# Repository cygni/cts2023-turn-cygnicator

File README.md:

# Introduction

Hello and welcome to the CTS 2023 embedded trail. In this trail you will be introduced to basic real-time system concepts and how to utilize them in FreeRTOS, a real-time system core for embedded devices. With these concepts, you will finalize a mini version of a car's telltale: brake, hazard and turn indicators will all be implemented using light and sound that can be controlled from a circuit board.

- [Introduction](#introduction)
  - [Raspberry Pi Pico](#raspberry-pi-pico)
  - [The Circuit Board (PCB)](#the-circuit-board-pcb)
    - [GPIO configuration table](#gpio-configuration-table)
  - [Workshop goals](#workshop-goals)
- [Workshop preparation](#workshop-preparation)
- [Workshop](#workshop)
  - [Preparation](#preparation)
  - [Prepare the development environment](#prepare-the-development-environment)
  - [How to build an image](#how-to-build-an-image)
  - [How to flash an image to Pico](#how-to-flash-an-image-to-pico)
    - [Step 1: Enter programming mode](#step-1-enter-programming-mode)
    - [Step 2: Flash image](#step-2-flash-image)
      - [Flashing using picotool](#flashing-using-picotool)
      - [Flashing by moving UF2 to mass-storage device](#flashing-by-moving-uf2-to-mass-storage-device)
- [Workshop starts here](#workshop-starts-here)
  - [Pico SDK API - Interrupt Handling](#pico-sdk-api---interrupt-handling)
    - [Cygnicator API](#cygnicator-api)
    - [FreeRTOS Task API](#freertos-task-api)
      - [xTaskCreate()](#xtaskcreate)
      - [vTaskStartScheduler()](#vtaskstartscheduler)
      - [vTaskDelay()](#vtaskdelay)
  - [Interrupt Handling](#interrupt-handling)
  - [Step 1: Handle button commands](#step-1-handle-button-commands)
    - [Task scheduling](#task-scheduling)
  - [Step 2: TURN LEFT and TURN RIGHT](#step-2-turn-left-and-turn-right)
    - [Syncing tasks](#syncing-tasks)
  - [Step 3: Hazzard](#step-3-hazzard)
  - [Step 4: Buzzer (TICK/TOCK sound)](#step-4-buzzer-ticktock-sound)
  - [Step 5: Periodicity](#step-5-periodicity)
    - [Handle shared resources](#handle-shared-resources)
  - [Step 6: Break button](#step-6-break-button)
  - [Step 7: One Task that controlls each LED row](#step-7-one-task-that-controlls-each-led-row)

## Raspberry Pi Pico

To realize the project, we will use a Raspberry Pi Pico. The Pico is based on the RP2040 microcontroller, which has a dual-core Arm Cortex-M0 CPU at 133Mhz (though clocked at 125Mhz by default). It has 264kB RAM and 2MB flash memory. The rest of the specifications can be read [here](https://www.raspberrypi.com/documentation/microcontrollers/rp2040.html). Pico has a logic voltage of 3.3V, which means that a GPIO pin that is high will have a voltage of 3.3V.

The board has 28 GPIO pins. GPIO pins are software-controlled connectors that can be used as input or output. Some pins can be used either as GPIO or for other functions such as I2C or PWM to configure it.

NOTE: When we refer to GPIO pins, we mean what is written in the green boxes in the reference image of the Picon, which corresponds to another physical pin (the gray boxes).

Some interesting pins:

- VBUS is connected directly to the micro-USB port and measures 5V when you have a USB adapter connected.
- VSYS is connected to VBUS via a diode. It is possible to drive the Pico directly by soldering a 1.8V to 5.5V voltage source to VSYS if you don't like USB. A Switching Mode Power Supply then converts the input voltage to 3.3V which powers the Pico.
- The 3V3_EN(able) pin can connect to ground to turn off the voltage converter, and then the Pico stops.
- The 3V3 pin is connected to the 3.3V operating voltage and can be used to drive components, the datasheet recommends not to draw more than 300mA.
The RUN pin can be used to restart the Pico, if connected to ground.

Others are described in the data sheet if you are interested.

The PICO has a BOOTSEL button. If you hold it down when you start the Pico, it is put into programmer mode, and appears as a portable USB disk.

## The Circuit Board (PCB)

On the circuit board, you can find a Raspberry Pi Pico that is routed in the PCB to be able to read input from 4 buttons and control 16 orange LEDs & 1 buzzer. Input/output is handled in the GPIO configuration that is *purposely* abstracted from the participants of this trail.

There is also a fifth button closest to the Pico board. This button ties RUN pin to ground when pressed which restarts the Pico.

### GPIO configuration table

Skip this section if you are not interested in which GPIO is connected to what.

| GPIO | GPIO CONFIG | HW desc |
| ---- |---- |------- |
| 2    | OUT | LED_FL0 |
| 3    | OUT | LED_FL1 |
| 4    | OUT | LED_FL2 |
| 5    | OUT | LED_FL3 |
| 6    | OUT | LED_FR0 |
| 7    | OUT | LED_FR1 |
| 8    | OUT | LED_FR2 |
| 9    | OUT | LED_FR3 |
| 10   | OUT | LED_RL0 |
| 11   | OUT | LED_RL1 |
| 12   | OUT | LED_RL2 |
| 13   | OUT | LED_RL3 |
| 19   | OUT | LED_RR0 |
| 18   | OUT | LED_RR1 |
| 17   | OUT | LED_RR2 |
| 16   | OUT | LED_RR3 |
| 14   | IN / PULL-UP | L_INDCR_BTN |
| 15   | IN / PULL-UP| L_INDCR_BTN |
| 20   | IN / PULL-UP| BRAKE_BTN |
| 21   | IN / PULL-UP| HAZARD_BTN |
| 22   | OUT / PWM | BUZZER |

Raspberry Pi Pico is not driving all LEDs directly, instead a MOSFET transistor is used for each LED to drive each individual LED using the +5V from the USB bus. This setup makes it possible for the 3.3V GPIO to control an LED with +5V forward voltage.

Simplification of the parameters:
- R_LED regulates the current that drives the LED i.e. the brightness
- R_PULLDOWN makes sure that the gate is closed by default. It "pulls" down the gate voltage to ground.
- R_GATE regulates the speed at which the MOSFET gate opens. (Other parameters affect this as well e.g. input impedance, internal GPIO resistors etc.)

## Workshop goals

| Button | Action | Expected outcome |
| ------ | ------ | --------- |
| Turn left | On press | Front left & rear left headlights toggles at a fixed interval. Buzzer plays a tick sound for each flash. |
| Turn right | On press | Front right & rear right headlights toggles at a fixed interval. Buzzer plays a tick sound for each flash. |
| Hazard | On press | All headlights headlights toggles at a fixed interval. Buzzer plays a tick sound for each flash. |
| Brake | On hold | All headlights are on. |

By fixed interval in the table above we mean it should be toggled at 1Hz. For the turn indicator, this would be according to the time diagram below. Note that we don't include tock sound. Cooler car brands do this. We don't know why:

Here is a gif of how the results will look like:
!!!TODO ADD A GIF WITH REFERENCE SOLUTION!!!

In a normal car, when the hazard is on and the brake is issued, the hazard continues after the brake has been released. In this workshop we do not require this behavior instead it's up to the designer how to handle this. You will see in the time diagrams later in the workshop that we suggest that you need to reissue the hazard after braking. The same goes for turn indicator.

# Workshop preparation

Prepare the workshop

## Preparation

This section is where you prepare and set up your development environment.
At the end of this section, you should be able to know where to add changes, and how to build and flash. To test the circuit board, we have provided a blinky code example that is going to be flashed onto the board.

Important folders and files:
```bash
# Your workspace, feel free to add more workspaces if needed.
firmware/turn-cygnicator

# ..we suggest you work in the same workspace throughout the workshop
# since every step builds on the previous one.

# Main entrypoint to your solution
firmware/turn-cygnicator/main.c

# Binary image that will be flashed onto the Raspberry Pi Pico
firmware/turn-cygnicator/turn-cygnicator.uf2

# Cygni turnindicator (Cygnicator) APIs
firmware/inc

# FreeRTOS kernel, you shouldn't need to touch this
firmware/lib/FreeRTOS-Kernel

# FreeRTOS configuration file for this project, you shouldn't need to touch this
firmware/inc/FreeRTOSConfig.h

```

## Prepare the development environment

In other words, build the docker image (`firmware/docker/Dockerfile`) that contains the FreeRTOS kernel, pico SDK, picotool and other tools/libraries that are needed.

Run this command in the root folder of this repository:
`docker build --build-arg UID="$(id -u)" -t rpisdk:latest docker/` or run
`build_docker.sh`

It takes a couple of minutes to download all dependencies, this command should only be run once.

## How to build an image

```bash
cd firmware

./build.sh

# Expected output
=== Output Files ===
./firmware/build/turn-cygnicator/turn-cygnicator.uf2
./firmware/build/blinky-demo/blinky-demo.uf2
```

## How to flash an image to Pico

### Step 1: Enter programming mode

Before flashing the image, the Pico needs to enter its programming mode.
This is done by holding the BOOTSEL button (1/RED) and pressing the RESET button (2/BLUE) once while the BOOTSEL button is still held down.

Now the Pico should have entered programming mode, it should appear to your host computer as a mass-storage device, like a USB memory stick. If it doesn't, you need to redo step 1.

### Step 2: Flash image

There are two alternatives to flash in this guide.

Either use:
- **picotool** provided in the docker image 
- **move UF2 image manually** to the mass-storage device.

#### Flashing using picotool

For convenience, we have included a flash script that shortens the command that is needed to flash.
Flash blinky sample code to verify that communication towards Pico works:
```bash
cd firmware

./flash.sh blinky-demo/blinky-demo.uf2
```

The expected results should look like this:

..by default this command flashes `turn-cygnicator` workspace, which is where your implementation is located. **Refer to this flash instruction during the workshop:**
```bash
cd firmware

./flash.sh
```

**Troubleshooting flash step:**
```bash
# Command that you run
$ docker run \
  --rm \
  -v $(pwd):$(pwd) \
  -w $(pwd)/build \
  --name rpibuilder \
  --privileged rpisdk:latest \
  /bin/picotool load -v -x blinky-demo/blinky-demo.uf2

# ------------------
# Expected output:
Loading into Flash: [==============================]  100%
Verifying Flash:    [==============================]  100%
  OK

The device was rebooted to start the application.

# ------------------
# If the Pico is not correctly set in BOOTSEL when running this command
# you instead get this:

No accessible RP2040 devices in BOOTSEL mode were found.

# ------------------
# We have also seen cases of this happening.
# Move on to "Flashing by moving UF2 to mass-storage device" instead.
ERROR: Unable to access device to reboot it; Use sudo or setup a udev rule
```

#### Flashing by moving UF2 to mass-storage device

The output file *.UF2 can also be flahed by moving it into Pico when it shows up as mass-storage device after putting the pico into BOOTSEL mode.

Important folders and files:
```bash
# Your workspace, feel free to add more workspaces if needed.
firmware/turn-cygnicator

# ..we suggest you work in the same workspace throughout the workshop
# since every step builds on the previous one.

# Main entrypoint to your solution
firmware/turn-cygnicator/main.c

# Binary image that will be flashed onto the Raspberry Pi Pico
firmware/turn-cygnicator/turn-cygnicator.uf2

# Cygni turnindicator (Cygnicator) APIs
firmware/inc

# FreeRTOS kernel, you shouldn't need to touch this
firmware/lib/FreeRTOS-Kernel

# FreeRTOS configuration file for this project, you shouldn't need to touch this
firmware/inc/FreeRTOSConfig.h

```

# Workshop starts here

Now the actual workshop starts

## Pico SDK API - Interrupt Handling

With the pico SDK you can configure IRQ handling for GPIO. In the example bellow we have configurad an IRQ for button TURN_LEFT which will print "Received an interrupt!" each time we click the button.

```C

void gpio_callback(uint gpio, uint32_t events) {
  printf("Received an interrupt on gpio %d with event %d! \n", gpio, events);
}

int main() {
  gpio_set_irq_enabled_with_callback(
    GPIO_BUTTON_TURN_LEFT, // gpio value
    GPIO_IRQ_EDGE_RISE,    // event mask
    true,                  // enabled
    &gpio_callback         // call back function
    );
}

```
The callback function protoype is defined as:
```C
typedef void(* gpio_irq_callback_t) (uint gpio, uint32_t event_mask)
```
you can have 1 to more interrupt events configured for same gpio
```C
// Event mask definition
enum gpio_irq_level {
  GPIO_IRQ_LEVEL_LOW = 0x1u,
  GPIO_IRQ_LEVEL_HIGH = 0x2u,
  GPIO_IRQ_EDGE_FALL = 0x4u,
  GPIO_IRQ_EDGE_RISE = 0x8u
};

//Eg:
gpio_set_irq_enabled_with_callback(
    GPIO_BUTTON_TURN_LEFT, // gpio value
    GPIO_IRQ_EDGE_RISE | GPIO_IRQ_EDGE_FALL, // event mask
    true,                  // enabled
    &gpio_callback         // call back function
    );

```

see reference: [gpio_set_irq_enabled_with_callback](https://www.raspberrypi.com/documentation/pico-sdk/hardware.html#ga6165f07f4b619dd08ea6dc97d069e78a)

### Cygnicator API

Since the main focus of this workshop will be freeRTOS, we have provided an API for you to use to control the buzzer and leds, **inc/cygnicator_headlights.h**

This API includes TYPES and GPIO mappings to eaze the process of turning on/off leds and use the buzzer: 

Here are some examples on how to use the API:

```C
// Turn on a led row:
for (int i = 0; i < HEADLIGHT_SIZE_LIMIT; i++) {
  gpio_put(gpio_headlight_map[FRONT_LEFT][i], 1);
}

// Check the state of a button
if (1 == gpio_get(gpio_button_map[BUTTON_LEFT_INDICATOR])) {
  printf("BUTTON_LEFT_INDICATOR is pressed \n");
} else {
  printf("BUTTON_LEFT_INDICATOR is not pressed");
}

//play a tone with the buzzer
void play_tone()
{
    const uint slice_num = pwm_gpio_to_slice_num(gpio_buzzer_map[BUZZER_FRONT]);
    pwm_set_wrap(slice_num, 8590);
    pwm_set_gpio_level(gpio_buzzer_map[BUZZER_FRONT], 8192);
}
```
### FreeRTOS Task API

A real-time application that uses an RTOS can be structured as a set of independent tasks. Each task executes within its own context with no coincidental dependency on other tasks within the system or the RTOS scheduler itself. Only one task within the application can be executing at any point in time and the real-time RTOS scheduler is responsible for deciding which task this should be. The RTOS scheduler may therefore repeatedly start and stop each task (swap each task in and out) as the application executes. As a task has no knowledge of the RTOS scheduler activity it is the responsibility of the real-time RTOS scheduler to ensure that the processor context (register values, stack contents, etc) when a task is swapped in is exactly that as when the same task was swapped out. To achieve this each task is provided with its own stack. When the task is swapped out the execution context is saved to the stack of that task so it can also be exactly restored when the same task is later swapped back in. 

This is a simplified task state diagram, containing only the states that we care about in this workshop:

Tasks are automatically in ready state when created. The RTOS scheduler decides what task to run at a time. An example of a blocking API call is vTaskDelay.

Looking for more information? These are the sources we have used:
| Description | Link |
| ------------ | --- |
| FreeRTOS what is a task? | [link](https://www.freertos.org/taskandcr.html) |
| FreeRTOS tasks states | [link](https://www.freertos.org/RTOS-task-states.html) |
| FreeRTOS Implementing tasks | [link](https://www.freertos.org/implementing-a-FreeRTOS-task.html) |
| FreeRTOS xTaskCreate API | [link](https://www.freertos.org/a00125.html) |
| FreeRTOS vTaskStartScheduler API | [link](https://www.freertos.org/a00132.html) |
| FreeRTOS vTaskDelay API | [link](https://www.freertos.org/a00127.html) |

#### xTaskCreate()

Create a new task and add it to the list of tasks that are ready to run.

#### vTaskStartScheduler()

Starts the RTOS scheduler. After calling the RTOS kernel has control over which tasks are executed and when. Normally this function is called from within main.c.

Example usage:
```cpp

static void vTaskCode(void *parameters) {
  for(;;)
  {
    // Do something here
  }

  // Tasks normally never exits
}

 void main()
 {
     // Tasks can be created before or after starting the RTOS
     xTaskCreate( vTaskCode,
                  "NAME",
                  STACK_SIZE,
                  NULL,
                  tskIDLE_PRIORITY,
                  NULL );

     // Start the real time scheduler.
     vTaskStartScheduler();

     // Will not get here unless there is insufficient RAM.
 }
```

#### vTaskDelay()

Delay a task for a given number of ticks. The actual time that the task remains blocked depends on the tick rate.

The function pdMS_TO_TICKS() can be used to calculate milliseconds to ticks using the tick rate with the resolution of one tick period.

Example:

```cpp
void vTaskFunction( void * pvParameters )
 {
    for( ;; )
    {
        /* Simply toggle the LED every 500ms, blocking between each toggle. */
        vToggleLED();

        // Block for 500ms
        vTaskDelay(pdMS_TO_TICKS(500));
    }
}
```

## Step 1: Handle button commands

Implement logic to handle the buttons TURN RIGHT, TURN LEFT, HAZZARD, BREAK

### Inter-task communication

Introduce FreeRTOS API to how to create tasks and communicate between tasks e.g. queues, mailboxes whatever
There are multiple ways/concepts that can be used for intertask communication such as queues, Binary Semaphores, Mutexes, Direct Task notification and stream/message buffers. 

Queues are the primary form and they can be used to send messages between tasks, and between interrupts and tasks. In most cases they are used as thread safe FIFO (First In First Out) buffers with new data being sent to the back of the queue, altough data can also be sent to the front of the queue.

### Queue example

```C
// Queue handler
static QueueHandle_t message_queue = NULL;

static void vTaskCode_rx(void *parameters) {
  int rx_value = 0;
  for(;;)
  {
    // block the rx task until a message is received on the queue with portMAX_DELAY
    xQueueReceive(
                    message_queue,
                    &rx_value,
                    portMAX_DELAY
                            );

    // if message received is equal to 1 then toggle the leds
    if (received == 1)  {
      vToggleLED();
    }
  }

  // Tasks normally never exits
}
static void vTaskCode_tx(void *parameters) {
  int tx_value = 0;
  for(;;)
  {
    // Send a 1 to message_queue every 500 ms. 
    vTaskDelay(pdMS_TO_TICKS(500));

    tx_value = 1;

    xQueueSend(
      message_queue,
      tx_value,
      0
    );

  }

  // Tasks normally never exits
}

 void main()
 {
    // create a queue that can hold 3 integers
    message_queue = xQueueCreate(3, sizeof(int));

    // Tasks can be created before or after starting the RTOS

    // Create RX task
     xTaskCreate( vTaskCode_rx,
                  "vTaskCode_rx", 
                  STACK_SIZE,
                  NULL,
                  tskRECEIVE_PRIORITY,
                  NULL );
    // Create TX task
      xTaskCreate( vTaskCode_tx,
                  "vTaskCode_tx",
                  STACK_SIZE,
                  NULL,
                  tskSEND_PRIORITY,
                  NULL );

     // Start the real time scheduler.
      vTaskStartScheduler();

     // Will not get here unless there is insufficient RAM.
 }
```
### Binary Semaphores

Binary sempahores are used for both mutual exclusion and synchronisation purposes. You can think of binary semaphore as a queue with one item.

```C
// Semaphore handler
SemaphoreHandle_t xSemaphore = NULL;

static void vTaskCode_a(void *parameters) {
  for(;;)
  {
    // Block task A until it can take the semaphore
    xSemaphoreTake( xSemaphore, portMAX_DELAY );
    // toggle the leds
    vToggleLED();
    
  }

  // Tasks normally never exits
}
static void vTaskCode_b(void *parameters) {
  for(;;)
  {

    // Unlock the semaphore every 500 ms. 
    vTaskDelay(pdMS_TO_TICKS(500));
    xSemaphoreGive(xSemaphore);
  }

  // Tasks normally never exits
}

 void main()
 {
    // Create the binary semaphore
    xSemaphore = xSemaphoreCreateBinary();

    // Tasks can be created before or after starting the RTOS

    // Create task A
     xTaskCreate( vTaskCode_a,
                  "vTaskCode_a", 
                  STACK_SIZE,
                  NULL,
                  tskIDLE_PRIORITY,
                  NULL );
    // Create task B
      xTaskCreate( vTaskCode_b,
                  "vTaskCode_b",
                  STACK_SIZE,
                  NULL,
                  tskIDLE_PRIORITY,
                  NULL );

     // Start the real time scheduler.
      vTaskStartScheduler();

     // Will not get here unless there is insufficient RAM.
 }
```
### Mutexes 

Mutexes are binary semaphores that include a priority inheritance mechanism. Whereas binary semaphores are the better choice for implementing synchronisation (between tasks or between tasks and an interrupt), mutexes are the better choice for implementing simple mutual exclusion (hence 'MUT'ual 'EX'clusion). 

```C
// Semaphore handler
SemaphoreHandle_t xSemaphore = NULL;

static void vTaskCode_a(void *parameters) {
  for(;;)
  {
    // Block task A until it can take the mutex
    xSemaphoreTake( xSemaphore, portMAX_DELAY );
    // toggle the leds
    vToggleLED();
    // give the mutex back
    xSemaphoreGive(xSemaphore);
  }

  // Tasks normally never exits
}
static void vTaskCode_b(void *parameters) {
  for(;;)
  {
    // Block task B until it can take the mutex
    xSemaphoreTake( xSemaphore, portMAX_DELAY );
    // Unlock the semaphore every 500 ms. 
    vTaskDelay(pdMS_TO_TICKS(500));
    // give the mutex back
    xSemaphoreGive(xSemaphore);
  }

  // Tasks normally never exits
}

 void main()
 {
    // Create the mutex
    xSemaphore = xSemaphoreCreateMutex();

    // Tasks can be created before or after starting the RTOS

    // Create task A
     xTaskCreate( vTaskCode_a,
                  "vTaskCode_a", 
                  STACK_SIZE,
                  NULL,
                  tskIDLE_PRIORITY,
                  NULL );
    // Create task B
      xTaskCreate( vTaskCode_b,
                  "vTaskCode_b",
                  STACK_SIZE,
                  NULL,
                  tskIDLE_PRIORITY,
                  NULL );

     // Start the real time scheduler.
      vTaskStartScheduler();

     // Will not get here unless there is insufficient RAM.
 }
```
### Direct Task notification 

A direct to task notification is an event sent directly to a task, rather than indirectly to a task via an intermediary object such as a queue, event group or semaphore. Sending a direct to task notification to a task sets the state of the target task notification to 'pending'. Just as a task can block on an intermediary object such as a semaphore to wait for that semaphore to be available, a task can block on a task notification to wait for that notification's state to become pending. 

You can use direct task notification as a lightweight:
* Binary Semaphore
* Counting Semaphore
* Event Group
* Mailbox

### stream/message buffers

Stream buffers are an RTOS task to RTOS task, and interrupt to task communication primitives. Unlike most other FreeRTOS communications primitives, they are optimised for single reader single writer scenarios, such as passing data from an interrupt service routine to a task, or from one microcontroller core to another on dual core CPUs. Data is passed by copy - the data is copied into the buffer by the sender and out of the buffer by the read.

Stream buffers pass a continuous stream of bytes. Message buffers pass variable sized but discrete messages. Message buffers use stream buffers for data transfer. 

| Description | Link |
| ------------ | --- |
| FreeRTOS Queues | [link](https://www.freertos.org/Embedded-RTOS-Queues.html) |
| FreeRTOS Queue API | [link](https://www.freertos.org/a00018.html) |
| FreeRTOS Binary Sempahores | [link](https://www.freertos.org/Embedded-RTOS-Binary-Semaphores.html) |
| FreeRTOS Mutex | [link](https://www.freertos.org/Real-time-embedded-RTOS-mutexes.html) |
| FreeRTOS Semaphore/mutex API | [link](https://www.freertos.org/a00113.html) |
| FreeRTOS Task Notifications | [link](https://www.freertos.org/RTOS-task-notifications.html) |
| FreeRTOS Task Notifications API | [link](https://www.freertos.org/RTOS-task-notification-API.html) |
| FreeRTOS Stream & Message Buffers | [link](https://www.freertos.org/RTOS-stream-message-buffers.html) |
| FreeRTOS Stream buffers API | [link](https://www.freertos.org/RTOS-stream-buffer-API.html) |
| FreeRTOS Message buffers API | [link](https://www.freertos.org/RTOS-message-buffer-API.html) |
## Step 2: TURN LEFT and TURN RIGHT

**Expected results:**

* When TURN LEFT button is pressed the LHS LEDs should turn ON and RHS LEDs turn OFF. If the button is pressed again, the LHS LEDs should turn OFF
* When TURN RIGHT button is pressed the RHS LEDs should turn on and LHS LEDs turn OFF. If the button is pressed again, the RHS LEDs should turn OFF

### Syncing tasks
Introduce FreeRTOS API on how to sync between tasks

## Step 3: Hazzard

**Expected results:**

* When HAZZARD button is pressed both LHS and RHS should turn ON at the same time. When button is pressed again, both sides should turn OFF at the same time.

## Step 4: Buzzer (TICK/TOCK sound)

During a Turn indication there is a sound being played in the car to notify the driver. Some brands wants only a "Tick" when the LEDs goes from OFF -> ON and some wants both "Tick" and "Tock". Tick when LEDs goes from OFF -> ON and Tick when led goes from ON -> OFF.

**Expected results:**
* During HAZZARD/TURN LEFT/TURN RIGHT commands there should be a Tick/Tock sound being played when the corresponding LEDs turns ON/OFF

## Step 5: Periodicity

Until this point the LEDs are able to turn ON/OFF with button commands. However in the car this feature is no.....

### Handle shared resources
Introduce FreeRTOS API to handle shared resources: semaphores etc.

**Expected results:**

## Step 6: Break button

**Expected results:**

## Step 7: One Task that controlls each LED row

T1 FRONT LEFT
T2 REAR LEFT
T3 FRONT RIGHT
T4 REAR RIGHT

**Expected results:**

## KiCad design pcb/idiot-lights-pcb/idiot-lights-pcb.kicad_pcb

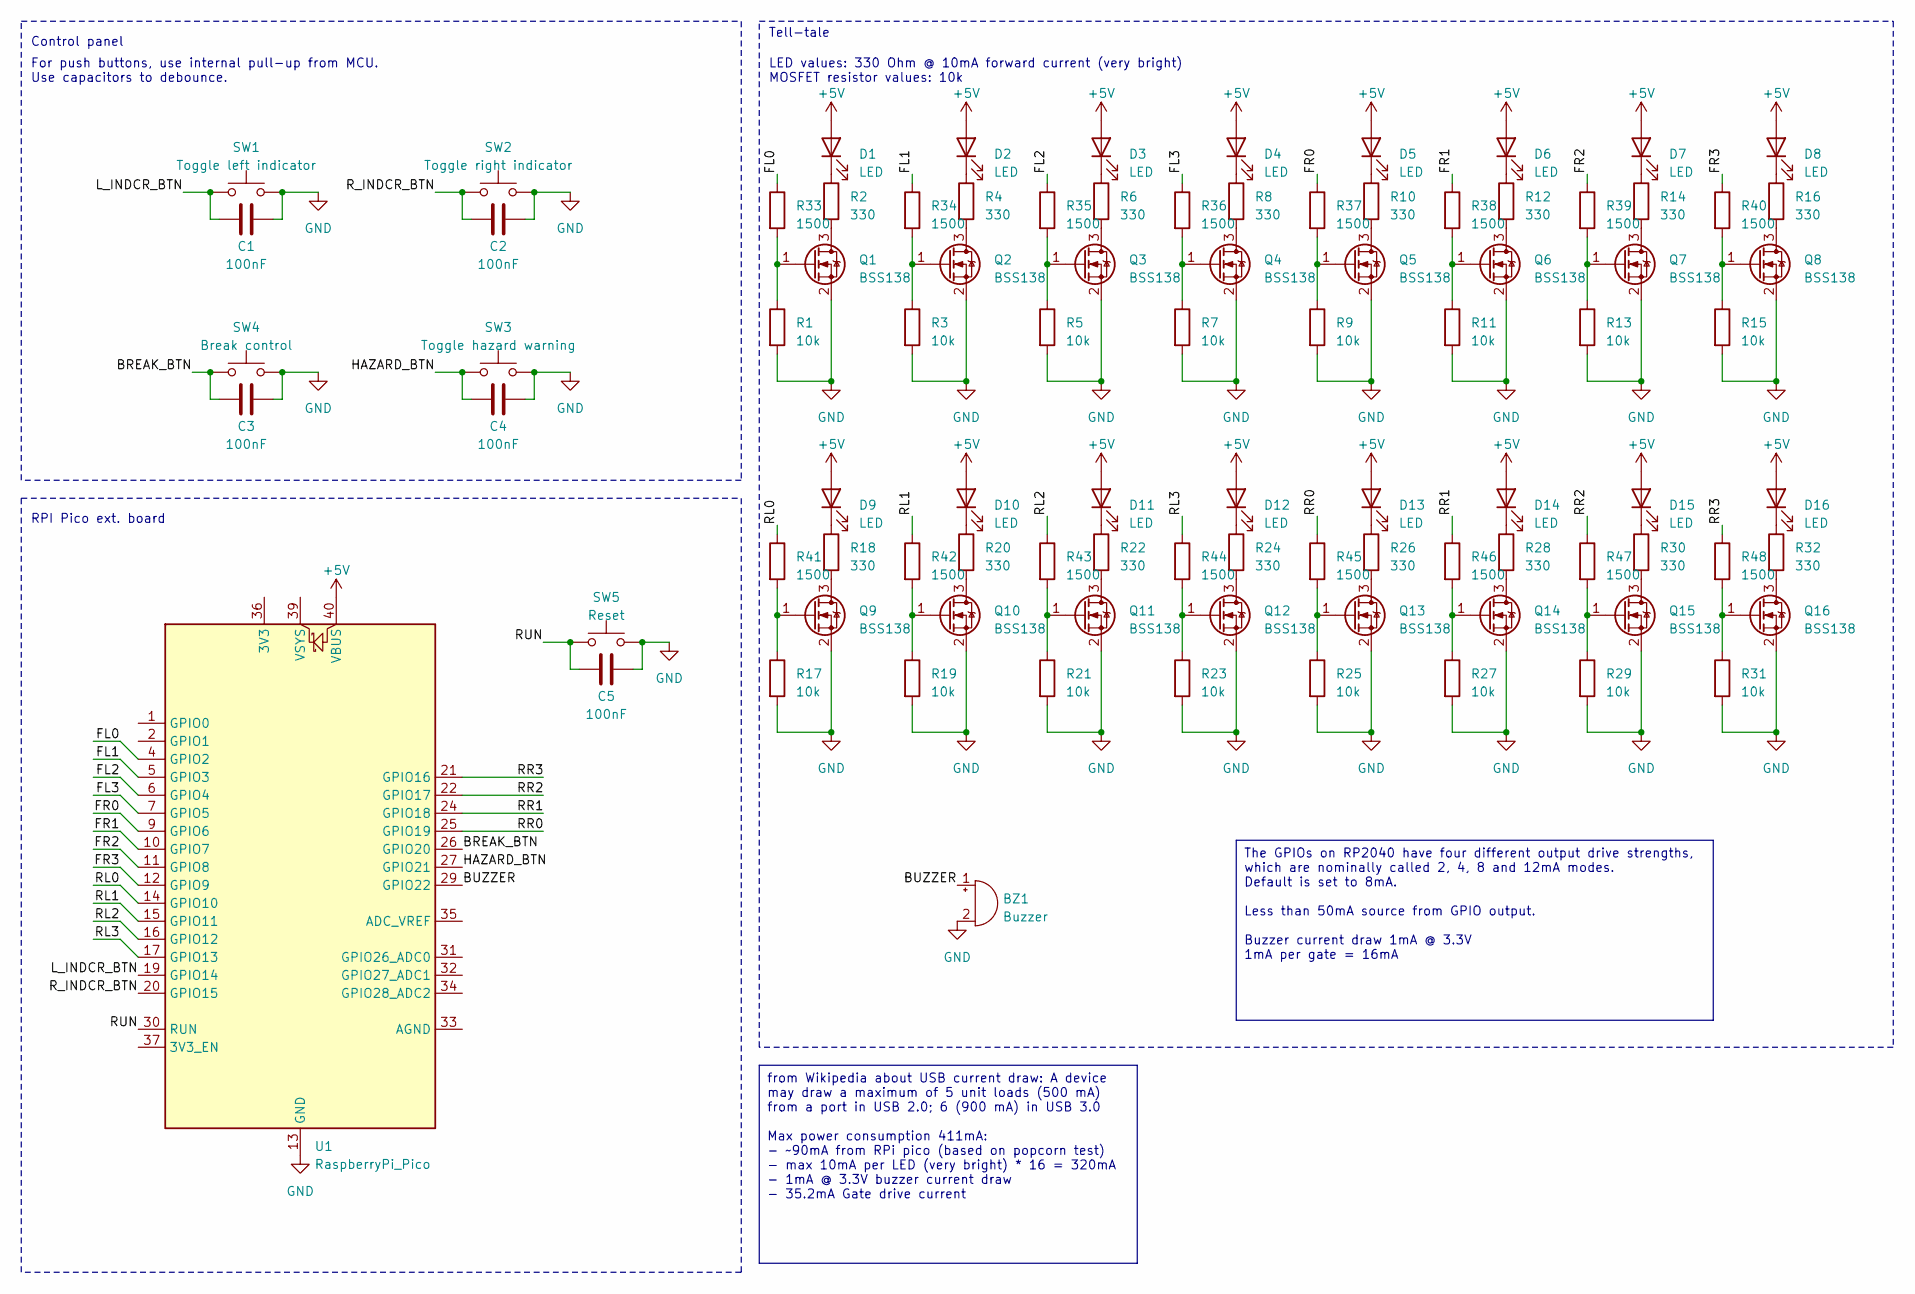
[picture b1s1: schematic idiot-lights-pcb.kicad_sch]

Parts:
BZ1: Buzzer; Buzzer_CUI_CPT-9019S-SMT; MPN CPT-9019B-SMT-TR
C1, C2, C3, C4, C5: 100nF; C_0603_1608Metric
D1, D2, D3, D4, D5, D6, D7, D8, D9, D10, D11, D12, D13, D14, D15, D16: LED; LED_0603_1608Metric_no_silk; MPN APTD1608SYCK/J3-PF
Q1, Q2, Q3, Q4, Q5, Q6, Q7, Q8, Q9, Q10, Q11, Q12, Q13, Q14, Q15, Q16: BSS138; SOT-23_no_silk; MPN BSS138
R1, R3, R5, R7, R9, R11, R13, R15, R17, R19, R21, R23, R25, R27, R29, R31: 10k; R_0603_1608Metric_no_silk
R2, R4, R6, R8, R10, R12, R14, R16, R18, R20, R22, R24, R26, R28, R30, R32: 330; R_0603_1608Metric_no_silk
R33, R34, R35, R36, R37, R38, R39, R40, R41, R42, R43, R44, R45, R46, R47, R48: 1500; R_0603_1608Metric_no_silk
SW1: Toggle left indicator; SW_SPST_PTS645; MPN 1301.9315
SW2: Toggle right indicator; SW_SPST_PTS645; MPN 1301.9315
SW3: Toggle hazard warning; SW_SPST_PTS645; MPN 1301.9315
SW4: Break control; SW_SPST_PTS645; MPN 1301.9315
SW5: Reset; SW_SPST_PTS645; MPN 1301.9315
U1: RaspberryPi_Pico; RaspberryPi_Pico_Common; MPN RASPBERRY PI PICO

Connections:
+5V: D1.2 (A), D2.2 (A), D3.2 (A), D4.2 (A), D5.2 (A), D6.2 (A), D7.2 (A), D8.2 (A), D9.2 (A), D10.2 (A), D11.2 (A), D12.2 (A), D13.2 (A), D14.2 (A), D15.2 (A), D16.2 (A), U1.40 (VBUS)
/BREAK_BTN: C3.1, SW4.1, U1.26 (GPIO20)
/BUZZER: BZ1.1 (-), U1.29 (GPIO22)
/FL0: R33.1, U1.4 (GPIO2)
/FL1: R34.1, U1.5 (GPIO3)
/FL2: R35.1, U1.6 (GPIO4)
/FL3: R36.1, U1.7 (GPIO5)
/FR0: R37.1, U1.9 (GPIO6)
/FR1: R38.1, U1.10 (GPIO7)
/FR2: R39.1, U1.11 (GPIO8)
/FR3: R40.1, U1.12 (GPIO9)
/HAZARD_BTN: C4.1, SW3.1, U1.27 (GPIO21)
/L_INDCR_BTN: C1.1, SW1.1, U1.19 (GPIO14)
/RL0: R41.1, U1.14 (GPIO10)
/RL1: R42.1, U1.15 (GPIO11)
/RL2: R43.1, U1.16 (GPIO12)
/RL3: R44.1, U1.17 (GPIO13)
/RR0: R45.1, U1.25 (GPIO19)
/RR1: R46.1, U1.24 (GPIO18)
/RR2: R47.1, U1.22 (GPIO17)
/RR3: R48.1, U1.21 (GPIO16)
/RUN: C5.1, SW5.1, U1.30 (RUN)
/R_INDCR_BTN: C2.1, SW2.1, U1.20 (GPIO15)
GND: BZ1.2 (+), C1.2, C2.2, C3.2, C4.2, C5.2, Q1.2 (S), Q2.2 (S), Q3.2 (S), Q4.2 (S), Q5.2 (S), Q6.2 (S), Q7.2 (S), Q8.2 (S), Q9.2 (S), Q10.2 (S), Q11.2 (S), Q12.2 (S), Q13.2 (S), Q14.2 (S), Q15.2 (S), Q16.2 (S), R1.2, R3.2, R5.2, R7.2, R9.2, R11.2, R13.2, R15.2, R17.2, R19.2, R21.2, R23.2, R25.2, R27.2, R29.2, R31.2, SW1.2, SW2.2, SW3.2, SW4.2, SW5.2, U1.3 (GND), U1.8 (GND), U1.13 (GND), U1.18 (GND), U1.23 (GND), U1.28 (GND), U1.38 (GND)
unnamed: D1.1 (K), R2.1
unnamed: D2.1 (K), R4.1
unnamed: D3.1 (K), R6.1
unnamed: D4.1 (K), R8.1
unnamed: D5.1 (K), R10.1
unnamed: D6.1 (K), R12.1
unnamed: D7.1 (K), R14.1
unnamed: D8.1 (K), R16.1
unnamed: D9.1 (K), R18.1
unnamed: D10.1 (K), R20.1
unnamed: D11.1 (K), R22.1
unnamed: D12.1 (K), R24.1
unnamed: D13.1 (K), R26.1
unnamed: D14.1 (K), R28.1
unnamed: D15.1 (K), R30.1
unnamed: D16.1 (K), R32.1
unnamed: Q1.3 (D), R2.2
unnamed: Q1.1 (G), R1.1, R33.2
unnamed: Q2.3 (D), R4.2
unnamed: Q2.1 (G), R3.1, R34.2
unnamed: Q3.3 (D), R6.2
unnamed: Q3.1 (G), R5.1, R35.2
unnamed: Q4.3 (D), R8.2
unnamed: Q4.1 (G), R7.1, R36.2
unnamed: Q5.3 (D), R10.2
unnamed: Q5.1 (G), R9.1, R37.2
unnamed: Q6.3 (D), R12.2
unnamed: Q6.1 (G), R11.1, R38.2
unnamed: Q7.3 (D), R14.2
unnamed: Q7.1 (G), R13.1, R39.2
unnamed: Q8.3 (D), R16.2
unnamed: Q8.1 (G), R15.1, R40.2
unnamed: Q9.3 (D), R18.2
unnamed: Q9.1 (G), R17.1, R41.2
unnamed: Q10.3 (D), R20.2
unnamed: Q10.1 (G), R19.1, R42.2
unnamed: Q11.3 (D), R22.2
unnamed: Q11.1 (G), R21.1, R43.2
unnamed: Q12.3 (D), R24.2
unnamed: Q12.1 (G), R23.1, R44.2
unnamed: Q13.3 (D), R26.2
unnamed: Q13.1 (G), R25.1, R45.2
unnamed: Q14.3 (D), R28.2
unnamed: Q14.1 (G), R27.1, R46.2
unnamed: Q15.3 (D), R30.2
unnamed: Q15.1 (G), R29.1, R47.2
unnamed: Q16.3 (D), R32.2
unnamed: Q16.1 (G), R31.1, R48.2

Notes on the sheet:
The GPIOs on RP2040 have four different output drive strengths, which are nominally called 2, 4, 8 and 12mA modes. Default is set to 8mA. Less than 50mA source from GPIO output. Buzzer current draw 1mA @ 3.3V 1mA per gate = 16mA
from Wikipedia about USB current draw: A device may draw a maximum of 5 unit loads (500 mA) from a port in USB 2.0; 6 (900 mA) in USB 3.0 Max power consumption 411mA: - ~90mA from RPi pico (based on popcorn test) - max 10mA per LED (very bright) * 16 = 320mA - 1mA @ 3.3V buzzer current draw - 35.2m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
RPI Pico ext. board
LED values: 330 Ohm @ 10mA forward current (very bright) MOSFET resistor values: 10k
Tell-tale
Control panel
For push buttons, use internal pull-up from MCU. Use capacitors to debounce.

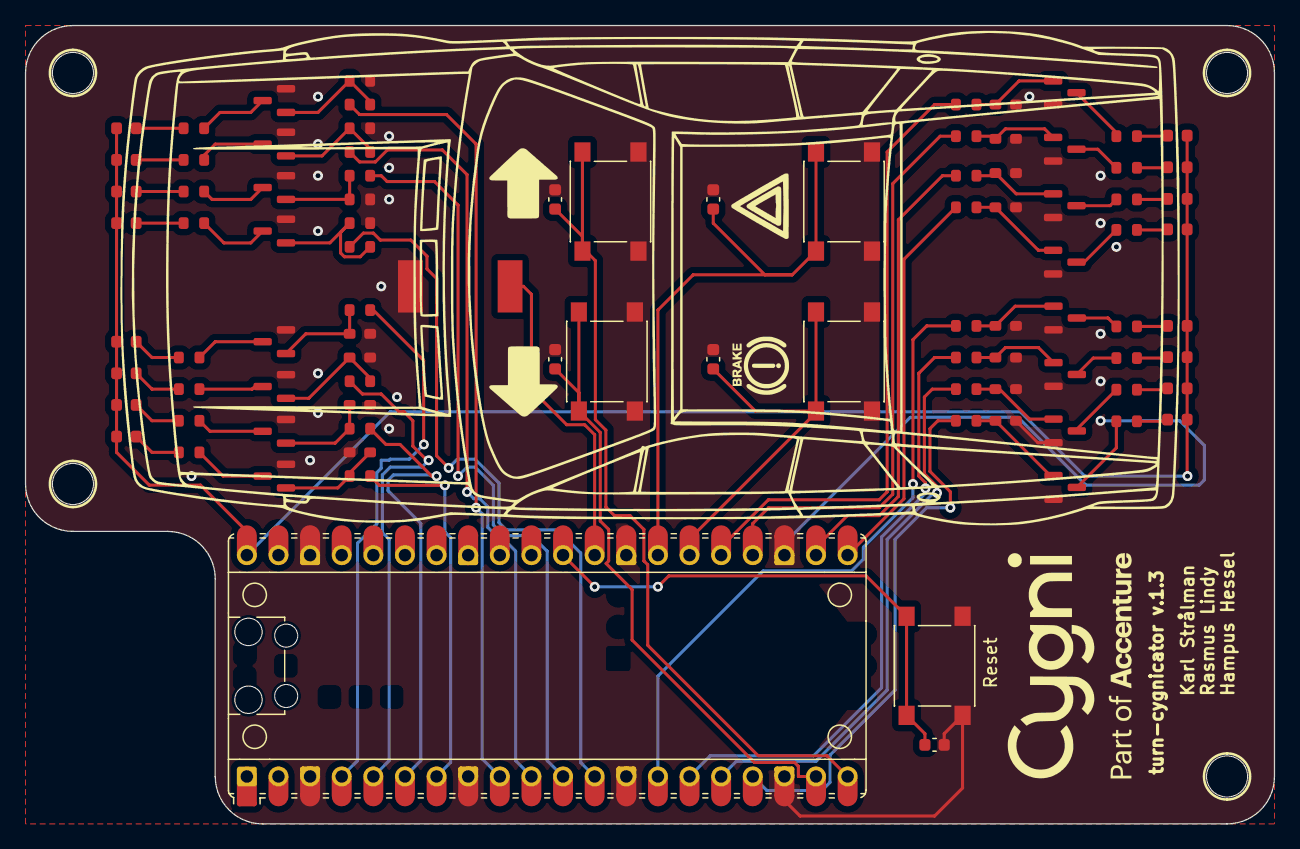
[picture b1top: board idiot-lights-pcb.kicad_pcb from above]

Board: 2 copper layers, 100.3 x 64.1 mm, 96 parts (0 on the bottom side), 72 nets.

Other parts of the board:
>NAME: >VALUE; STAND-OFF
>NAME#2, >NAME#3, >NAME#4: >VALUE; STAND-OFF

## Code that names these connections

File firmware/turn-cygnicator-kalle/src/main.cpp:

#include <FreeRTOS.h>
#include <event_groups.h>
#include <inttypes.h>
#include <queue.h>
#include <semphr.h>
#include <stdint.h>
#include <stdio.h>
#include <task.h>

#include <climits>

#include "cygnicator_headlights.h"
#include "hardware/gpio.h"
#include "hardware/pwm.h"
#include "pico/stdio.h"
#include "pico/time.h"
#include "pico/types.h"
#include "portmacro.h"

#include "led.hpp"
#include "telltale.hpp"
#include "buzzer.hpp"

enum GPIO_PINS : uint32_t {
  L_INDCR_BTN = 14,
  R_INDCR_BTN = 15,
  BRAKE_BTN = 20,
  HAZARD_BTN = 21,
  BUZZER = 22,
};

QueueHandle_t mailbox;

TaskHandle_t hLEDControllerFrontRight;
TaskHandle_t hLEDControllerFrontLeft;
TaskHandle_t hLEDControllerRearRight;
TaskHandle_t hLEDControllerRearLeft;
TaskHandle_t hButtonHandler;

TaskHandle_t notifyTasks[] = {hLEDControllerFrontRight, hLEDControllerFrontLeft,
                              hLEDControllerRearRight, hLEDControllerRearLeft};

static void tHeadlight(void *parameters) {
  HeadlightTaskParameters *headlightParameters =
      (HeadlightTaskParameters *)(parameters);

  uint32_t telltaleCmd;
  uint8_t const *leds = headlights[headlightParameters->headlightRow];

  while (true) {
    xQueuePeek(mailbox, &telltaleCmd, portMAX_DELAY);

    handleTelltaleCmd(headlightParameters, (TellTaleCmd)telltaleCmd, leds);

    vTaskDelay(250);
  }
}

static bool readButtonNotify(ButtonAction *action) {
  bool btnPressed = !gpio_get(action->gpio);

  if (btnPressed) {
    for (TaskHandle_t task : notifyTasks) {
      printf("[tButtonHandler]: Notifying cmd %d\n", action->cmd);
      xQueueOverwrite(mailbox, &action->cmd);
    }
  }
  return btnPressed;
}

static void tButtonHandler(void *parameters) {
  ButtonTaskParameters *btnParameters = (ButtonTaskParameters *)parameters;

  while (true) {
    vTaskDelay(1);

    // Continue to next cycle if one event is triggered.
    // This prevents multiple events in the mailbox at the same time.
    if (readButtonNotify(&btnParameters->onHazard)) {
      continue;
    }

    if (readButtonNotify(&btnParameters->onTurnRight)) {
      continue;
    }

    if (readButtonNotify(&btnParameters->onTurnLeft)) {
      continue;
    }

    if (readButtonNotify(&btnParameters->onBrake)) {
      // TODO send event if brake off
      continue;
    }
  }
}

int main(void) {
  stdio_init_all();

  gpio_init_mask(gpio_output_pins_mask);
  gpio_init_mask(gpio_input_pins_mask);
  gpio_set_dir_out_masked(gpio_output_pins_mask);
  gpio_set_dir_in_masked(gpio_input_pins_mask);

  gpio_set_function(gpio_buzzer_map[BUZZER_FRONT], GPIO_FUNC_PWM);
  uint8_t const slice_num = pwm_gpio_to_slice_num(gpio_buzzer_map[BUZZER_FRONT]);
  pwm_set_enabled(slice_num, true);

  // say hello, so we know the program is running
  play_tone();
  gpio_set_mask(gpio_output_pins_mask);
  gpio_set_mask(gpio_input_pins_mask);
  sleep_ms(1000);
  stop_tone();
  gpio_clr_mask(gpio_input_pins_mask);
  gpio_clr_mask(gpio_output_pins_mask);

  gpio_init(L_INDCR_BTN);
  gpio_init(R_INDCR_BTN);
  gpio_init(HAZARD_BTN);
  gpio_init(BRAKE_BTN);
  gpio_set_dir(L_INDCR_BTN, GPIO_IN);
  gpio_set_dir(R_INDCR_BTN, GPIO_IN);
  gpio_set_dir(HAZARD_BTN, GPIO_IN);
  gpio_set_dir(BRAKE_BTN, GPIO_IN);
  gpio_pull_up(L_INDCR_BTN);
  gpio_pull_up(R_INDCR_BTN);
  gpio_pull_up(HAZARD_BTN);
  gpio_pull_up(BRAKE_BTN);

  mailbox = xQueueCreate(1, sizeof(uint32_t));

  EventGroupHandle_t onHazardEventGroup = xEventGroupCreate();
  EventGroupHandle_t onBrakeEventGroup = xEventGroupCreate();
  EventGroupHandle_t onTurnLeftEventGroup = xEventGroupCreate();
  EventGroupHandle_t onTurnRightEventGroup = xEventGroupCreate();

  HeadlightTaskParameters paramsFrontRight = {
      .onHazard = {.action = HeadlightRowAction::SIMULTANEOUSLY,
                   .eventGroupHandle = onHazardEventGroup,
                   .thisTasksSyncBit = FRONT_RIGHT_SYNC_BIT,
                   .allSyncBits = ALL_SYNC_BITS},
      .onBrake = {.action = HeadlightRowAction::NOP},
      .onTurnRight = {.action = HeadlightRowAction::LEFT_TO_RIGHT,
                      .eventGroupHandle = onTurnRightEventGroup,
                      .thisTasksSyncBit = FRONT_RIGHT_SYNC_BIT,
                      .allSyncBits = RIGHT_SYNC_BITS},
      .onTurnLeft = {.action = HeadlightRowAction::NOP},
      .headlightRow = FRONT_RIGHT,
  };
  HeadlightTaskParameters paramsFrontLeft = {
      .onHazard = {.action = HeadlightRowAction::SIMULTANEOUSLY,
                   .eventGroupHandle = onHazardEventGroup,
                   .thisTasksSyncBit = FRONT_LEFT_SYNC_BIT,
                   .allSyncBits = ALL_SYNC_BITS},
      .onBrake = {.action = HeadlightRowAction::NOP},
      .onTurnRight = {.action = HeadlightRowAction::NOP,
                      .eventGroupHandle = onTurnRightEventGroup},
      .onTurnLeft = {.action = HeadlightRowAction::RIGHT_TO_LEFT,
                     .eventGroupHandle = onTurnLeftEventGroup,
                     .thisTasksSyncBit = FRONT_LEFT_SYNC_BIT,
                     .allSyncBits = LEFT_SYNC_BITS},
      .headlightRow = FRONT_LEFT,
  };
  HeadlightTaskParameters paramsRearRight = {
      .onHazard = {.action = HeadlightRowAction::SIMULTANEOUSLY,
                   .eventGroupHandle = onHazardEventGroup,
                   .thisTasksSyncBit = REAR_RIGHT_SYNC_BIT,
                   .allSyncBits = ALL_SYNC_BITS},
      .onBrake = {.action = HeadlightRowAction::SIMULTANEOUSLY,
                  .eventGroupHandle = onBrakeEventGroup,
                  .thisTasksSyncBit = REAR_RIGHT_SYNC_BIT,
                  .allSyncBits = REAR_SYNC_BITS},
      .onTurnRight = {.action = HeadlightRowAction::LEFT_TO_RIGHT,
                      .eventGroupHandle = onTurnRightEventGroup,
                      .thisTasksSyncBit = REAR_RIGHT_SYNC_BIT,
                      .allSyncBits = RIGHT_SYNC_BITS},
      .onTurnLeft = {.action = HeadlightRowAction::NOP},
      .headlightRow = REAR_RIGHT,
  };
  HeadlightTaskParameters paramsRearLeft = {
      .onHazard = {.action = HeadlightRowAction::SIMULTANEOUSLY,
                   .eventGroupHandle = onHazardEventGroup,
                   .thisTasksSyncBit = REAR_LEFT_SYNC_BIT,
                   .allSyncBits = ALL_SYNC_BITS},
      .onBrake = {.action = HeadlightRowAction::SIMULTANEOUSLY,
                  .eventGroupHandle = onBrakeEventGroup,
                  .thisTasksSyncBit = REAR_LEFT_SYNC_BIT,
                  .allSyncBits = REAR_SYNC_BITS},
      .onTurnRight = {.action = HeadlightRowAction::NOP},
      .onTurnLeft = {.action = HeadlightRowAction::RIGHT_TO_LEFT,
                     .eventGroupHandle = onTurnLeftEventGroup,
                     .thisTasksSyncBit = REAR_LEFT_SYNC_BIT,
                     .allSyncBits = LEFT_SYNC_BITS},
      .headlightRow = REAR_LEFT,
  };
  ButtonTaskParameters paramsButton = {
      .onHazard = {HAZARD_BTN, TellTaleCmd::Hazard},
      .onBrake = {BRAKE_BTN, TellTaleCmd::Brake},
      .onTurnRight = {R_INDCR_BTN, TellTaleCmd::Right},
      .onTurnLeft = {L_INDCR_BTN, TellTaleCmd::Left},
  };

  xTaskCreate(tHeadlight, headlightRowStrings[FRONT_RIGHT],
              configMINIMAL_STACK_SIZE, (void *)&paramsFrontRight, 0,
              &hLEDControllerFrontRight);
  xTaskCreate(tHeadlight, headlightRowStrings[FRONT_LEFT],
              configMINIMAL_STACK_SIZE, (void *)&paramsFrontLeft, 0,
              &hLEDControllerFrontLeft);
  xTaskCreate(tHeadlight, headlightRowStrings[REAR_LEFT],
              configMINIMAL_STACK_SIZE, (void *)&paramsRearLeft, 0,
              &hLEDControllerRearRight);
  xTaskCreate(tHeadlight, headlightRowStrings[REAR_RIGHT],
              configMINIMAL_STACK_SIZE, (void *)&paramsRearRight, 0,
              &hLEDControllerRearLeft);

  xTaskCreate(tButtonHandler, "Buttonhandlertask", configMINIMAL_STACK_SIZE,
              &paramsButton, 0, &hButtonHandler);

  printf("Started");
  vTaskStartScheduler();
}

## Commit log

2023-06-02 Add gitignore for kicad files
2023-06-06 Update gitignore and add kicad lib
2023-06-06 Add cygni logo and telltale symbol libs
2023-06-06 Remove unused lib
2023-06-06 Update gitignore
2023-06-10 Version 1.0 of idiot lights
2023-06-10 Switch from THT to SMD for multiple components
    Buzzer & LED lights arrays
2023-06-10 Adjust spacing on diode symbols in schematic to be more aligned
2023-06-10 Add rpi pico libraries
2023-06-10 Add pico SMD solder mounts
2023-06-10 Replace buzzer with CPT
2023-06-12 Add mosfet controlling every LED and let 5V rail handle powering
2023-06-12 Add MPN field and generate bom
2023-06-17 Replace car silk with free model
    Source https://www.freecads.com/en/transportation/car-top-view-00000998
2023-06-17 Add github link QR code on B.Silk
    Remove rearview mirror on car (too bulky)
    Fix project paths
2023-06-17 Add gate resistors and re-reoute symbols
    Bump version text to v.1.2
2023-06-19 Initial fw configuration setup
    Automatically generated from
2023-06-19 Initial project structure
2023-06-19 nokewngoewnifewnfew
2023-06-19 Include FreeRTOS in build
2023-06-20 Fix resistor values
2023-06-20 Add WIP control leds
2023-07-28 Set footprint type for RPI pico to avoid confusion when ordering SMD soldered
2023-08-25 Revert "Set footprint type for RPI pico to avoid confusion when ordering SMD soldered"
    This reverts commit 52f91ab8c31850276995a09216dcdc41241bf451.
2023-08-28 add PCB schematic as pdf
2023-08-28 Add picotool to docker, add build instructions
2023-08-28 add Docker building image instruction
2023-08-28 add instruction for flashing pico with picotool
2023-08-29 Add build script for easy building
2023-08-29 Increase LED resistor values - dim LEDs
    Set RPI pico property to THT again
2023-08-30 Add skeleton for Hampus solution, vscode settings
2023-08-30 Hampus implementation wip
2023-09-01 Bump pcb version
2023-09-02 Add smaller QR code and remove corner for usb cable
2023-09-03 Kalle implemenation wip
2023-09-19 Fix FreeRtosConfig.h, add devcontainer, CMake fixes
2023-09-20 Hampus WIP
2023-09-20 Hampus implementation: more progress
2023-09-20 Move popd before make
2023-09-22 Refactor and add eventgroup for sync
2023-09-24 Rasmus solution
2023-09-24 Hampus version 1.0
2023-09-26 Adjust to light LED like Rasmus and Hampus
2023-10-02 Fix build.sh
2023-10-03 WIP README
2023-10-03 Add puml directory and to readme
2023-10-04 Hide time axis on pumls
2023-10-04 plantuml time diagrams
2023-10-04 WIP Preparation steps
2023-10-04 Add sample blinky project and gifs
    We need more gifs
2023-10-04 Adjust blinky gif
2023-10-04 Add how-to flash in readme and script to flash
2023-10-04 Change owner of /bin/picotool to builder
2023-10-04 WIP Add introductory FreeRTOS information
2023-10-05 Add vTaskDelay desc
2023-10-05 Adding state machine logic (draft)
2023-10-05 Something that is compiling atleast
2023-10-05 Change build.sh
    define queue messages and ids
2023-10-05 almost working solution
2023-10-06 Remove and add instructions on pico-sdk vscode setup
2023-10-10 WIP car print curses
    Jack freertos into this
2023-10-10 Move pthread link to simulator.cmake
2023-10-10 WIP move to headlight gpios
2023-10-10 Basic emulator
2023-10-10 WIP simulation car goes blinky blink
2023-10-10 Map fake gpios to ASCII car
2023-10-10 Use pthread directly instead of FreeRTOS scheduling
2023-10-10 keeeeypad
2023-10-10 hehehwiwehiw
2023-10-10 Make turn-cygnicator-reference build with simulator
2023-10-10 Switch pthread to FreeRtos for simulator
2023-10-10 Latest coolest GUI CLI
2023-10-10 Tillbakakaka
2023-10-10 Add hint for start logo screen
2023-10-10 Add console buffer
2023-10-10 use vsprintf in sim_printf
2023-10-10 Restore README
2023-10-10 Describe Cygnicator API
    explain how to flash with uf2 and mass-storage
2023-10-10 Add queue example
2023-10-10 Add mutex description
2023-10-10 Some cleanup of simulator code
2023-10-11 task notifications stream and message buffers
2023-10-11 Fix dockerfile for E.M.O.J.I. 😘😘
2023-10-11 Make blinky demo work in simulator
2023-10-12 Direct task notificaton
    Stream and message buffers
2023-10-12 more readme more description on each step
    some gifs for expected results
2023-10-14 Support polling buttons in simulator
2023-10-16 Correction in readme
2023-10-23 default CMake that attendees will use
2023-10-23 Add init function to attendees
2023-10-23 Add polling example
2023-10-24 Fix compilation error for turn-cygnicator
2023-10-24 Restore rasmus solution
2023-10-24 Readme updates
2023-10-24 spelling
2023-10-25 Suggestion on how to fix brake issue when leds are not on somtimes.
    increase to 500 ms so we get periodicity of 1 sec
    change led to roll when switched on and turn off all
    simulatinously
    changed spelling hazzard to hazard
    added more state switch traces
    add gpio_put_masked in simulator api
2023-10-25 Fix uml diagrams to line up with 2 hz
    remove c_cpp_properties.json
    fix kalle comment in readme
    update readme with 2 hz
2023-10-26 remove firmware/lib
2023-10-26 Move README to docs
2023-10-26 change from gif to webm
2023-10-26 remove brake and button switch gif
2023-10-26 fix webm
2023-10-26 remove webm
2023-10-26 Update README.md
    drag drop webm
2023-10-26 Refactor readme and add run sim script
2023-10-26 more readme fixes and other shit
2023-10-26 Update README.md
    fix webm
2023-10-26 Add section about VSCode Devcontainer
2023-11-02 Fix expected results for step 7
2023-11-03 Almost compiling with traceAlyzer
2023-11-03 add webm files to repo
2023-11-03 Embedd webm
2023-11-03 link directly to webm
2023-11-03 test with video tag
2023-11-03 Image links with thumbnail
2023-11-03 fix other final.webm link
2023-11-03 Webm fix (#11)
    * Image links with thumbnail
    ---------
2023-11-06 BSD compatible build.sh
2023-11-06 Minor update to README.md
2023-11-06 fix path for docker build
2023-11-06 Add helper scripts and instructions to run picocom
2023-11-07 Add serial instructions for Mac/Windows
2023-11-07 Picocom docs (#12)
    * Add helper scripts and instructions to run picocom
    * Add serial instructions for Mac/Windows
    ---------
2023-11-09 Emphasize need to clean build folder, fix heading levels
2023-11-09 remove docker build script mention
2023-11-10 Default target -> hardware
2023-11-10 Fix callback example
2023-11-10 Update skeleton code
2023-11-10 Complementary notes in Readme
2023-11-10 Mention dialout for Linux
2023-11-10 mention groupmod logout
2023-11-10 Mention ISR-functions
2023-11-12 txValue -> &txValue
